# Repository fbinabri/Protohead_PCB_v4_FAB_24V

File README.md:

# Protohead_PCB_v4_FAB_24V

This repository includes an alternative pcb for this DIY HEAD:
https://github.com/imarin2/ProtoHead_v4

that in addition to what is explained in that other repository, also makes available the 24 V and the servo1 to the user.

# So what is this in short?

Just a PCB, not a full head, featuring:
- Full Kicad project (for libraries look here: https://github.com/imarin2/FABHeadLibraries)
- Flatcam project for insulation milling
- Heekscad project for cutout and slots
- The gcode to manufacture the PCB with a FABtotum (the gcode is for my tools, see wiki: http://wiki.fabtotum.com/doku.php?id=pcb_milling_workflow#preparation_tools)

In pictures:

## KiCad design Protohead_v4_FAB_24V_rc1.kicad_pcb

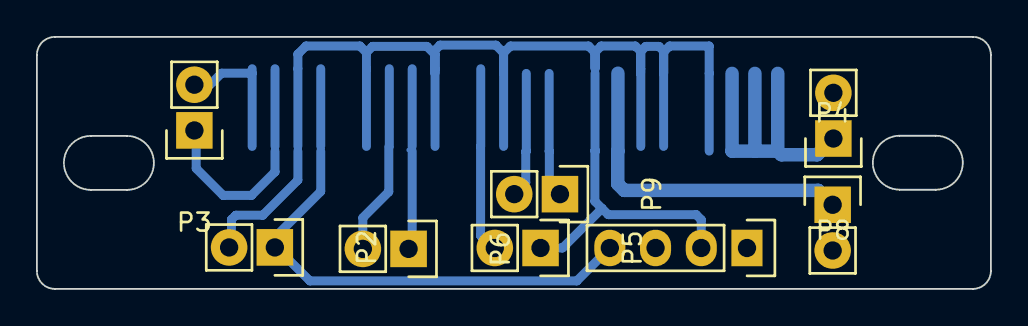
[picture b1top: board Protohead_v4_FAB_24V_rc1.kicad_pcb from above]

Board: 2 copper layers, 53.0 x 14.0 mm, 9 parts (1 on the bottom side), 11 nets.

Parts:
P1: FABTOTUM_HEAD_CONNECTOR; IntegratedBourns_smd
P2: 5VDC; Pin_Header_Straight_1x02
P3: THERMISTOR; Pin_Header_Straight_1x02
P4: HEATER; Pin_Header_Straight_1x02
P5: BLOWER; Pin_Header_Straight_1x02
P6: I2C; Pin_Header_Straight_1x02
P7: Arduino_Mini_RAW_GND_RST_VCC; Socket_Strip_Straight_1x04
P8: 24VDC; Pin_Header_Straight_1x02
P9: SERVO1; Pin_Header_Straight_1x02

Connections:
GND: P1.4, P1.5, P1.6, P1.8, P1.11, P1.13, P1.16, P1.18, P2.2, P4.2, P5.1, P7.2, P8.2
unnamed: P1.1, P1.2, P1.3, P8.1
unnamed: P1.7, P4.1
unnamed: P1.9, P9.1
unnamed: P1.10, P9.2
unnamed: P1.12, P5.2
unnamed: P1.14, P6.1
unnamed: P1.15, P6.2
unnamed: P1.17, P2.1, P7.4
unnamed: P1.19, P3.1
unnamed: P1.20, P3.2

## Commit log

2015-09-17 KiCAD PCB project + Flatcam + Heekscam
2015-09-26 PCBnew screenshot
2015-09-29 Updated paths to new Kicad 3D standards
    Now the libraries include .3dshapes extension for the folder of the 3d models
